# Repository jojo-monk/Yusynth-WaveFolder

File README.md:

# Yusynth-WaveFolder
Adaptation du Yusynth [WaveFolder](http://yusynth.net/Modular/index_en.html) au format Eurorack
Testé et fonctionnel

[Build document](https://htmlpreview.github.io/?https://github.com/jojo-monk/Yusynth-WaveFolder/blob/main/ibom.html)

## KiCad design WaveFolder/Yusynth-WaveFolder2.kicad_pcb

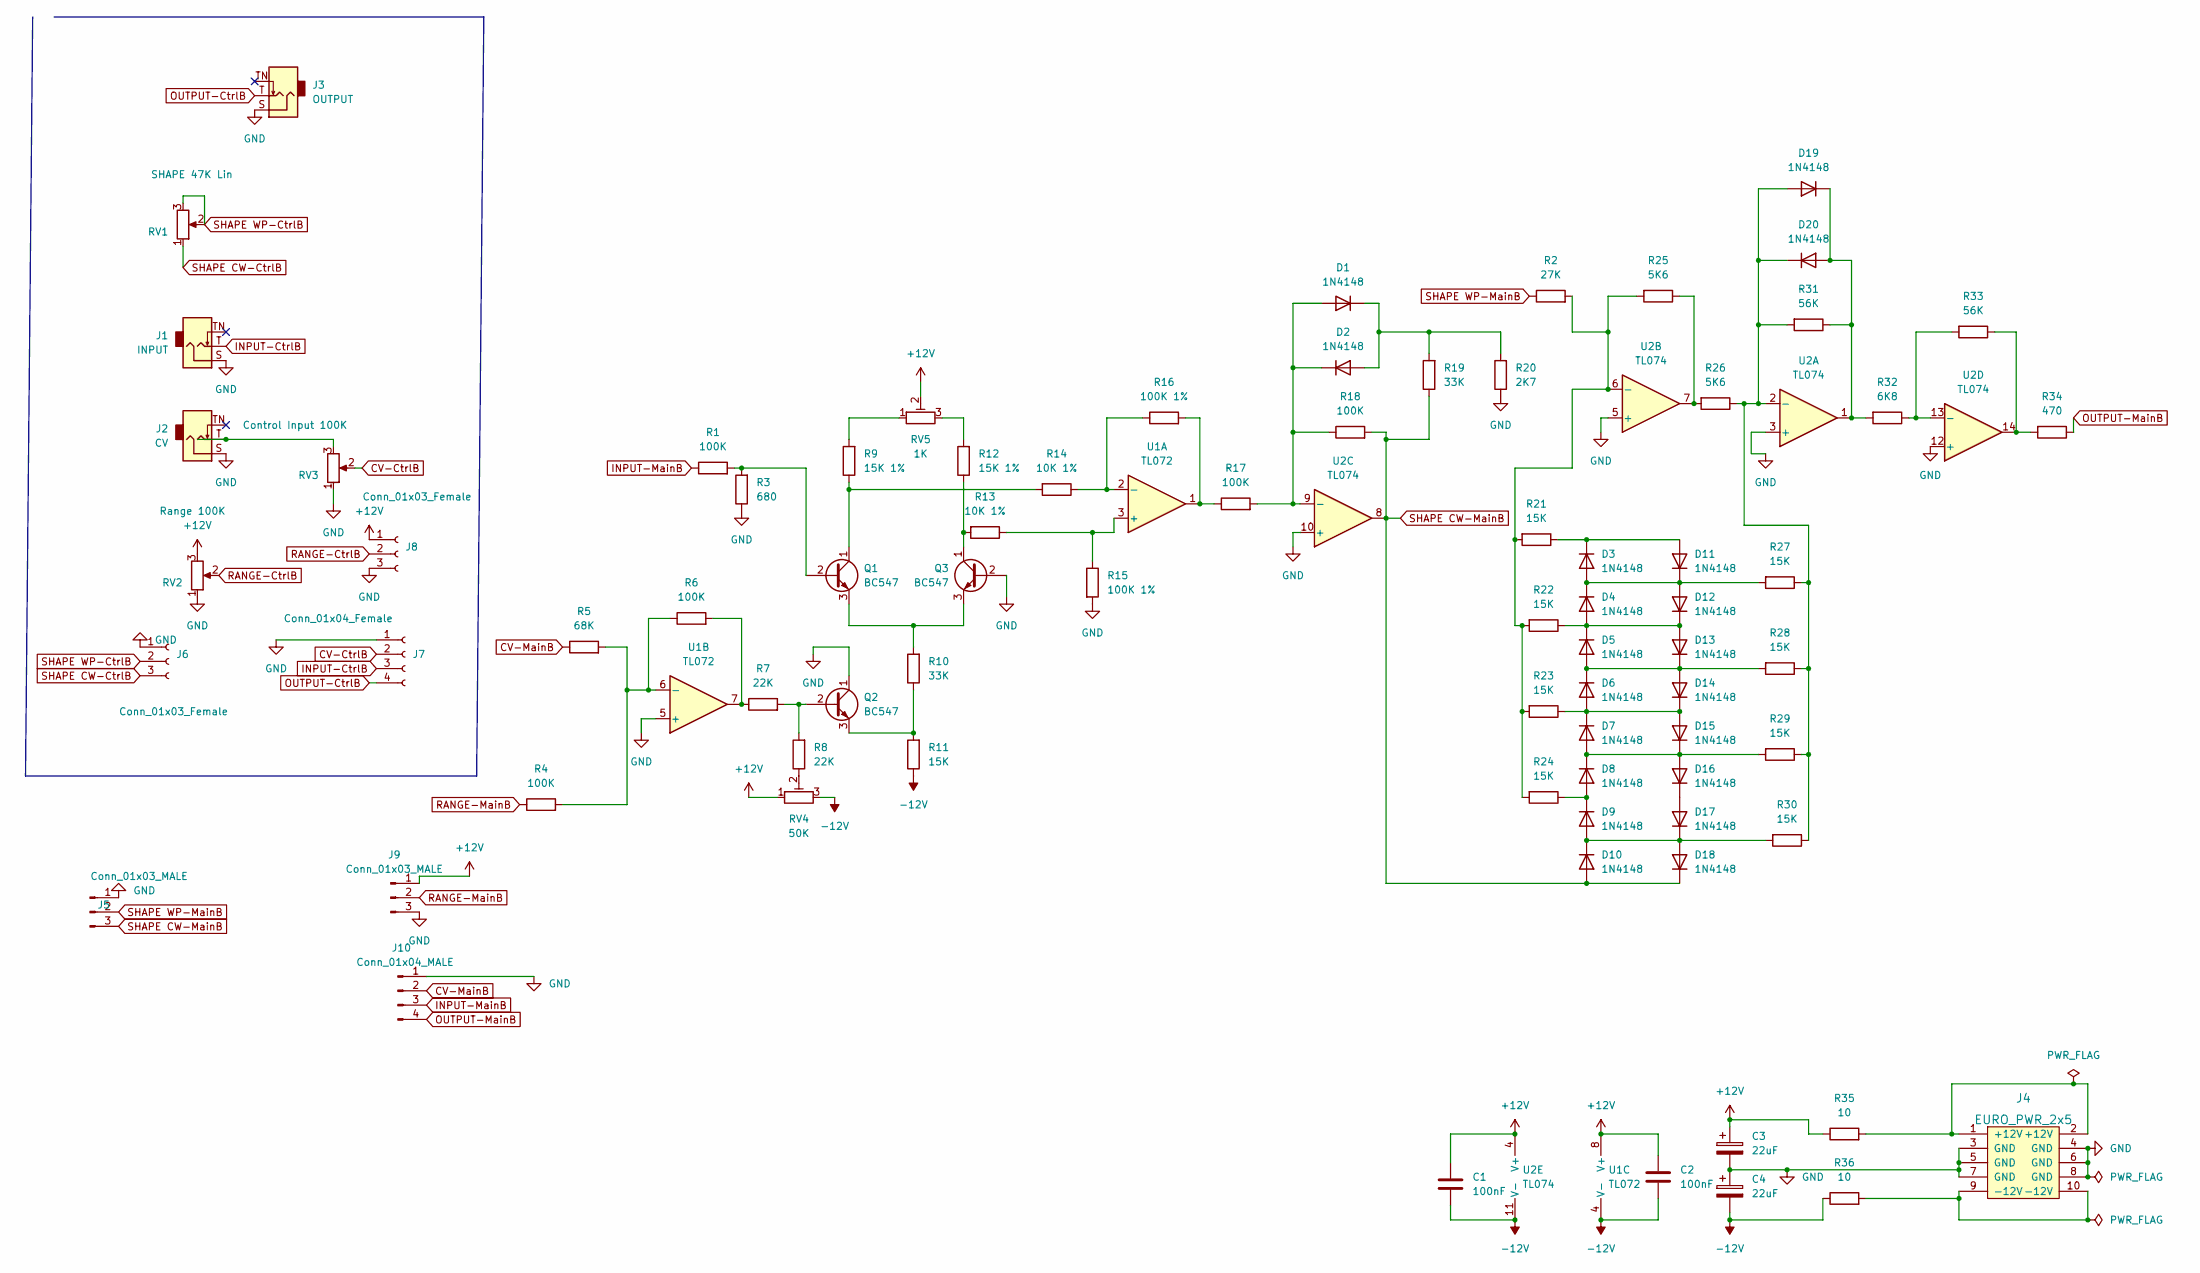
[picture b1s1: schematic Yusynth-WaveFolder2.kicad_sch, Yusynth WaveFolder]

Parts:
C1, C2: 100nF; C_Disc_D5.0mm_W2.5mm_P5.00mm
C3, C4: 22uF; CP_Radial_D5.0mm_P2.00mm
D1, D2, D3, D4, D5, D6, D7, D8, D9, D10, D11, D12, D13, D14, D15, D16, D17, D18, D19, D20: 1N4148; D_DO-35_SOD27_P7.62mm_Horizontal
J1: INPUT; Jack_3.5mm_QingPu_WQP-PJ398SM_Vertical
J2: CV; Jack_3.5mm_QingPu_WQP-PJ398SM_Vertical
J3: OUTPUT; Jack_3.5mm_QingPu_WQP-PJ398SM_Vertical
J4: EURO_PWR_2x5; Eurorack_power_header
J5, J9: Conn_01x03_MALE; PinHeader_1x03_P2.54mm_Vertical
J6, J8: Conn_01x03_Female; PinHeader_1x03_P2.54mm_Vertical
J7: Conn_01x04_Female; PinHeader_1x04_P2.54mm_Vertical
J10: Conn_01x04_MALE; PinHeader_1x04_P2.54mm_Vertical
Q1, Q2, Q3: BC547; TO-92_HandSolder
R1, R4, R6, R17, R18: 100K; R_Axial_DIN0207_L6.3mm_D2.5mm_P5.08mm_Vertical
R2: 27K; R_Axial_DIN0207_L6.3mm_D2.5mm_P5.08mm_Vertical
R3: 680; R_Axial_DIN0207_L6.3mm_D2.5mm_P5.08mm_Vertical
R5: 68K; R_Axial_DIN0207_L6.3mm_D2.5mm_P5.08mm_Vertical
R7, R8: 22K; R_Axial_DIN0207_L6.3mm_D2.5mm_P5.08mm_Vertical
R9, R12: 15K 1%; R_Axial_DIN0207_L6.3mm_D2.5mm_P5.08mm_Vertical
R10, R19: 33K; R_Axial_DIN0207_L6.3mm_D2.5mm_P5.08mm_Vertical
R11, R21, R22, R23, R24, R27, R28, R29, R30: 15K; R_Axial_DIN0207_L6.3mm_D2.5mm_P5.08mm_Vertical
R13, R14: 10K 1%; R_Axial_DIN0207_L6.3mm_D2.5mm_P5.08mm_Vertical
R15, R16: 100K 1%; R_Axial_DIN0207_L6.3mm_D2.5mm_P5.08mm_Vertical
R20: 2K7; R_Axial_DIN0207_L6.3mm_D2.5mm_P5.08mm_Vertical
R25, R26: 5K6; R_Axial_DIN0207_L6.3mm_D2.5mm_P5.08mm_Vertical
R31, R33: 56K; R_Axial_DIN0207_L6.3mm_D2.5mm_P5.08mm_Vertical
R32: 6K8; R_Axial_DIN0207_L6.3mm_D2.5mm_P5.08mm_Vertical
R34: 470; R_Axial_DIN0207_L6.3mm_D2.5mm_P5.08mm_Vertical
R35, R36: 10; R_Axial_DIN0207_L6.3mm_D2.5mm_P5.08mm_Vertical
RV1: SHAPE 47K Lin; Potentiometer_Alpha_RD901F-40-00D_Single_Vertical
RV2: Range 100K; Potentiometer_Alpha_RD901F-40-00D_Single_Vertical
RV3: Control Input 100K; Potentiometer_Alpha_RD901F-40-00D_Single_Vertical
RV4: 50K; Potentiometer_Bourns_3266Y_Vertical
RV5: 1K; Potentiometer_Bourns_3266Y_Vertical
U1: TL072; DIP-8_W7.62mm_LongPads
U2: TL074; DIP-14_W7.62mm_LongPads

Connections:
+12V: C1.1, C2.1, C3.1, J8.1, J9.1, R35.1, RV2.3, RV4.1, RV5.2, U1.8 (V+), U2.4 (V+)
-12V: C1.2, C2.2, C4.2, R11.1, R36.1, RV4.3, U1.4 (V-), U2.11 (V-)
CV-CtrlB: J7.2, RV3.2
CV-MainB: J10.2, R5.1
GND: C3.2, C4.1, J1.S, J2.S, J3.S, J4.3 (GND), J4.4 (GND), J4.5 (GND), J4.6 (GND), J4.7 (GND), J4.8 (GND), J5.1, J6.1, J7.1, J8.3, J9.3, J10.1, Q2.1 (C), Q3.2 (B), R3.1, R15.2, R20.1, RV2.1, RV3.1, U1.5 (+), U2.3 (+), U2.5 (+), U2.10 (+), U2.12 (+)
INPUT-CtrlB: J1.T, J7.3
INPUT-MainB: J10.3, R1.1
unnamed: D1.1 (K), D2.2 (A), R19.2, R20.2
unnamed: D1.2 (A), D2.1 (K), R17.2, R18.1, U2.9 (-)
unnamed: D8.2 (A), D9.1 (K), R24.1
unnamed: D9.2 (A), D10.1 (K), D17.1 (K), D18.2 (A), R30.2
unnamed: D3.2 (A), D4.1 (K), D11.1 (K), D12.2 (A), R27.2
unnamed: D3.1 (K), D11.2 (A), R21.1
unnamed: D4.2 (A), D5.1 (K), D12.1 (K), D13.2 (A), R22.1
unnamed: D5.2 (A), D6.1 (K), D13.1 (K), D14.2 (A), R28.2
unnamed: D6.2 (A), D7.1 (K), D14.1 (K), D15.2 (A), R23.1
unnamed: D7.2 (A), D8.1 (K), D15.1 (K), D16.2 (A), R29.2
unnamed: D16.1 (K), D17.2 (A)
unnamed: D19.1 (K), D20.2 (A), R31.1, R32.2, U2.1
unnamed: D19.2 (A), D20.1 (K), R26.1, R27.1, R28.1, R29.1, R30.1, R31.2, U2.2 (-)
unnamed: J2.T, RV3.3
unnamed: J4.1 (+12V), J4.2 (+12V), R35.2
unnamed: J4.9 (-12V), J4.10 (-12V), R36.2
unnamed: Q1.1 (C), R9.1, R14.2
unnamed: Q1.2 (B), R1.2, R3.2
unnamed: Q1.3 (E), Q3.3 (E), R10.2
unnamed: Q2.2 (B), R7.2, R8.2
unnamed: Q2.3 (E), R10.1, R11.2
unnamed: Q3.1 (C), R12.1, R13.2
unnamed: R2.2, R21.2, R22.2, R23.2, R24.2, R25.2, U2.6 (-)
unnamed: R4.2, R5.2, R6.1, U1.6 (-)
unnamed: R6.2, R7.1, U1.7
unnamed: R8.1, RV4.2
unnamed: R9.2, RV5.1
unnamed: R12.2, RV5.3
unnamed: R13.1, R15.1, U1.3 (+)
unnamed: R14.1, R16.1, U1.2 (-)
unnamed: R16.2, R17.1, U1.1
unnamed: R25.1, R26.2, U2.7
unnamed: R32.1, R33.2, U2.13 (-)
unnamed: R33.1, R34.2, U2.14
OUTPUT-CtrlB: J3.T, J7.4
OUTPUT-MainB: J10.4, R34.1
RANGE-CtrlB: J8.2, RV2.2
RANGE-MainB: J9.2, R4.1
SHAPE CW-CtrlB: J6.3, RV1.1
SHAPE CW-MainB: D10.2 (A), D18.1 (K), J5.3, R18.2, R19.1, U2.8
SHAPE WP-CtrlB: J6.2, RV1.2, RV1.3
SHAPE WP-MainB: J5.2, R2.1

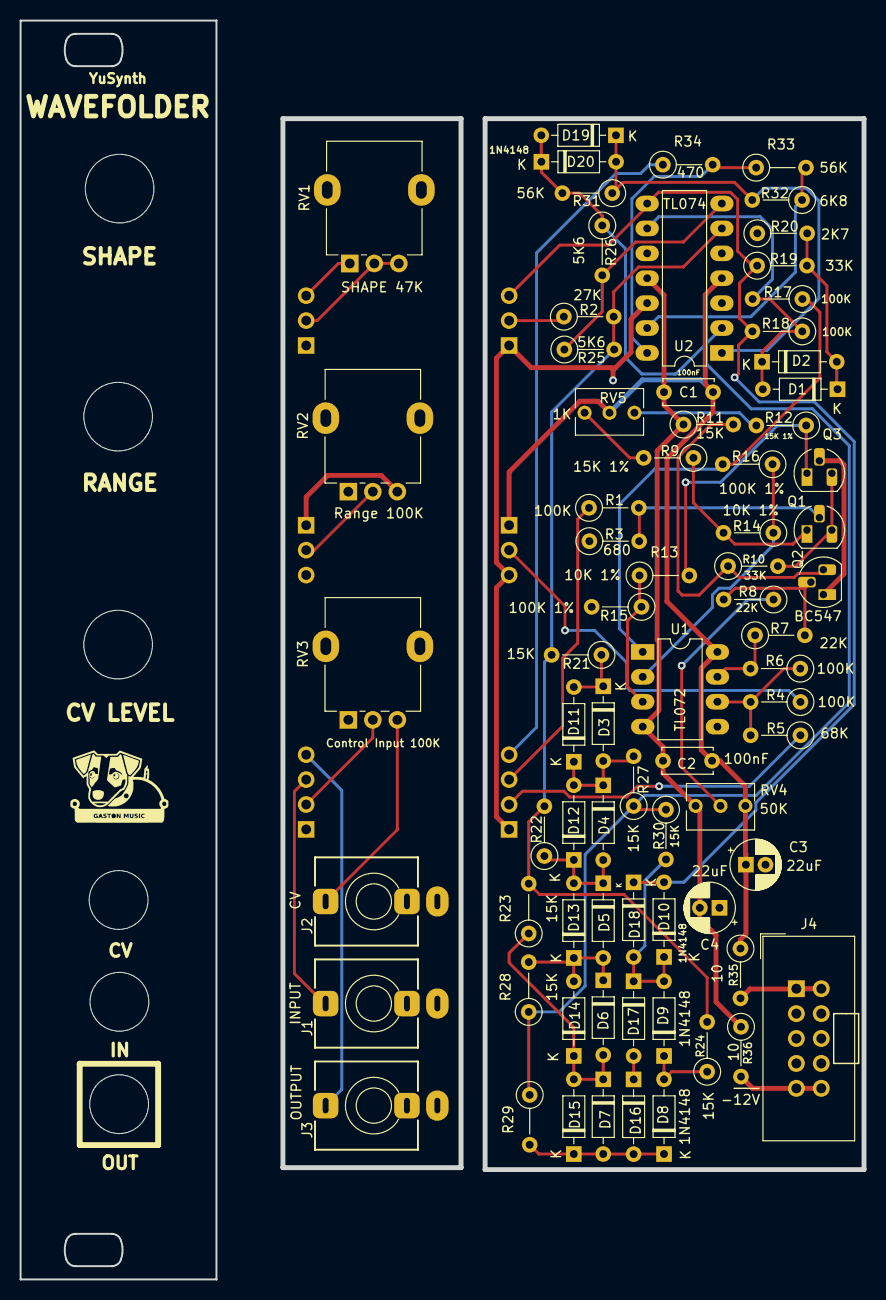
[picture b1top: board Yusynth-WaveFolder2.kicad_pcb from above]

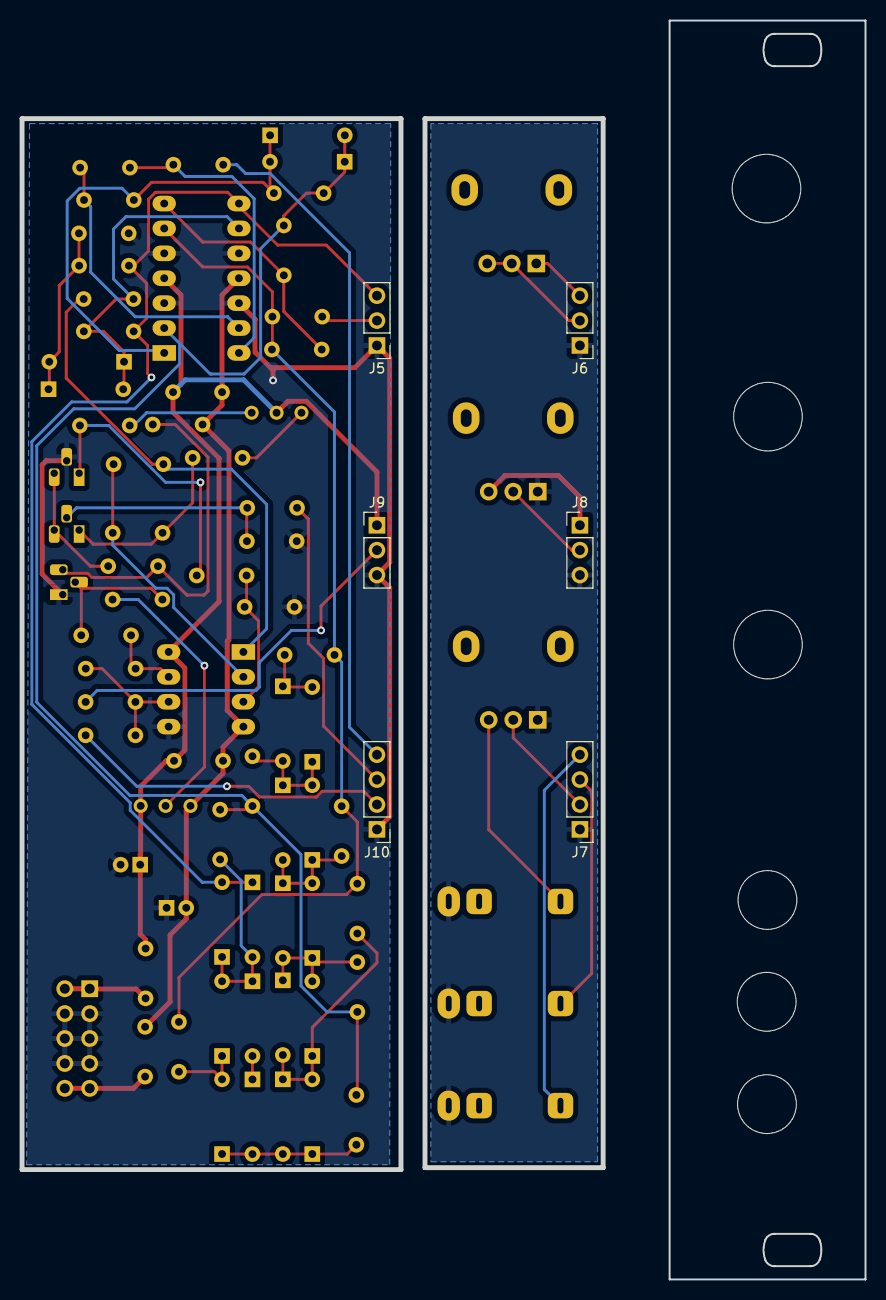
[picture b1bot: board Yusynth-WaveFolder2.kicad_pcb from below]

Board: 2 copper layers, 85.9 x 128.1 mm, 80 parts (6 on the bottom side), 49 nets.

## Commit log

2023-08-12 Wavefolder
2023-08-12 ajout readme
2023-08-12 suppression dossier bom
2023-08-12 deplacement
2023-09-13 add photos
